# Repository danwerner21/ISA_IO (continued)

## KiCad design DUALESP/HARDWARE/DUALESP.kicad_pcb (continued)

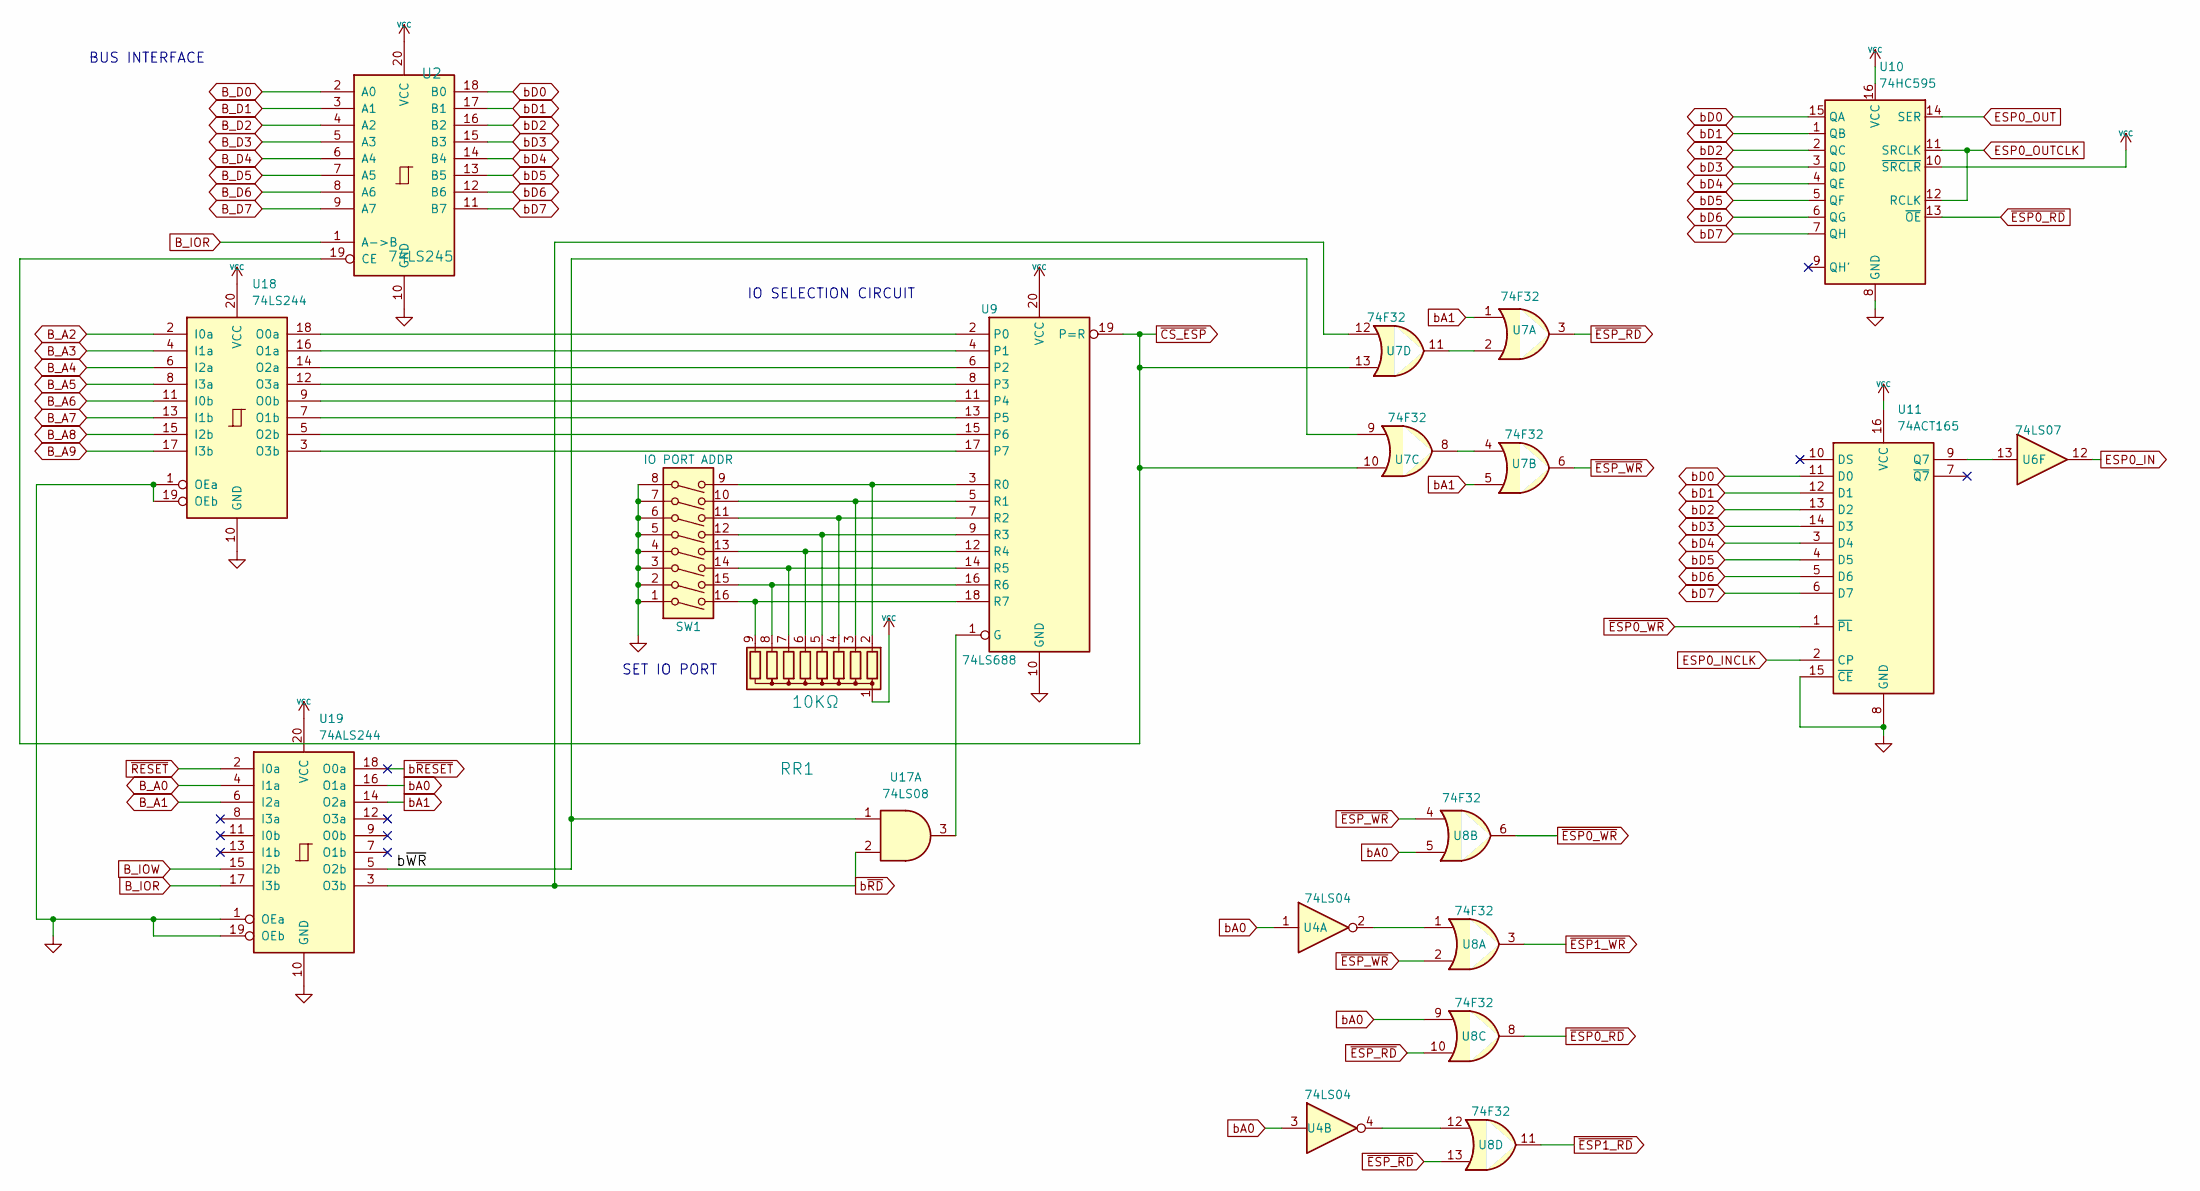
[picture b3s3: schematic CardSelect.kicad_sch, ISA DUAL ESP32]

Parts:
RR1: 10KΩ; R_Array_SIP9
SW1: IO PORT ADDR; STD_DDW_DIP16
U2: 74LS245; STD_DDW_DIP20
U4: 74LS04; STD_DDW_DIP14
U6: 74LS07; STD_DDW_DIP14
U7, U8: 74F32; STD_DDW_DIP14
U9: 74LS688; STD_DDW_DIP20
U10: 74HC595; STD_DDW_DIP16
U11: 74ACT165; STD_DDW_DIP16
U17: 74LS08; STD_DDW_DIP14
U18: 74LS244; STD_DDW_DIP20
U19: 74ALS244; STD_DDW_DIP20

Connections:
/CardSelect/b~WR: U7.9, U17.1, U19.5 (O2b)
B_A0: U19.4 (I1a); also elsewhere on the board
B_A1: U19.6 (I2a); also elsewhere on the board
B_A2: U18.2 (I0a); also elsewhere on the board
B_A3: U18.4 (I1a); also elsewhere on the board
B_A4: U18.6 (I2a); also elsewhere on the board
B_A5: U18.8 (I3a); also elsewhere on the board
B_A6: U18.11 (I0b); also elsewhere on the board
B_A7: U18.13 (I1b); also elsewhere on the board
B_A8: U18.15 (I2b); also elsewhere on the board
B_A9: U18.17 (I3b); also elsewhere on the board
B_D0: U2.2 (A0); also elsewhere on the board
B_D1: U2.3 (A1); also elsewhere on the board
B_D2: U2.4 (A2); also elsewhere on the board
B_D3: U2.5 (A3); also elsewhere on the board
B_D4: U2.6 (A4); also elsewhere on the board
B_D5: U2.7 (A5); also elsewhere on the board
B_D6: U2.8 (A6); also elsewhere on the board
B_D7: U2.9 (A7); also elsewhere on the board
B_IOR: U2.1 (A->B), U19.17 (I3b); also elsewhere on the board
B_IOW: U19.15 (I2b); also elsewhere on the board
ESP0_IN: U6.12; also elsewhere on the board
ESP0_INCLK: U11.2 (CP); also elsewhere on the board
ESP0_OUT: U10.14 (SER); also elsewhere on the board
ESP0_OUTCLK: U10.11 (SRCLK), U10.12 (RCLK); also elsewhere on the board
GND: SW1.1, SW1.2, SW1.3, SW1.4, SW1.5, SW1.6, SW1.7, SW1.8, U2.10 (GND), U9.10 (GND), U10.8 (GND), U11.8 (GND), U11.15 (~CE), U18.1 (OEa), U18.10 (GND), U18.19 (OEb), U19.1 (OEa), U19.10 (GND), U19.19 (OEb); also elsewhere on the board
unnamed: RR1.2 (R1), SW1.9, U9.3 (R0)
unnamed: RR1.3 (R2), SW1.10, U9.5 (R1)
unnamed: RR1.4 (R3), SW1.11, U9.7 (R2)
unnamed: RR1.5 (R4), SW1.12, U9.9 (R3)
unnamed: RR1.6 (R5), SW1.13, U9.12 (R4)
unnamed: RR1.7 (R6), SW1.14, U9.14 (R5)
unnamed: RR1.8 (R7), SW1.15, U9.16 (R6)
unnamed: RR1.9 (R8), SW1.16, U9.18 (R7)
unnamed: U4.2, U8.1
unnamed: U4.4, U8.12
unnamed: U7.4, U7.8
unnamed: U7.2, U7.11
unnamed: U9.1 (G), U17.3
unnamed: U6.13, U11.9 (Q7)
unnamed: U9.2 (P0), U18.18 (O0a)
unnamed: U9.11 (P4), U18.9 (O0b)
unnamed: U9.4 (P1), U18.16 (O1a)
unnamed: U9.13 (P5), U18.7 (O1b)
unnamed: U9.6 (P2), U18.14 (O2a)
unnamed: U9.15 (P6), U18.5 (O2b)
unnamed: U9.8 (P3), U18.12 (O3a)
unnamed: U9.17 (P7), U18.3 (O3b)
VCC: RR1.1 (common), U2.20 (VCC), U9.20 (VCC), U10.10 (~SRCLR), U10.16 (VCC), U11.16 (VCC), U18.20 (VCC), U19.20 (VCC); also elsewhere on the board
bA0: U4.1, U4.3, U8.5, U8.9, U19.16 (O1a)
bA1: U7.1, U7.5, U19.14 (O2a); also elsewhere on the board
bD0: U2.18 (B0), U10.15 (QA), U11.11 (D0); also elsewhere on the board
bD1: U2.17 (B1), U10.1 (QB), U11.12 (D1); also elsewhere on the board
bD2: U2.16 (B2), U10.2 (QC), U11.13 (D2); also elsewhere on the board
bD3: U2.15 (B3), U10.3 (QD), U11.14 (D3); also elsewhere on the board
bD4: U2.14 (B4), U10.4 (QE), U11.3 (D4); also elsewhere on the board
bD5: U2.13 (B5), U10.5 (QF), U11.4 (D5); also elsewhere on the board
bD6: U2.12 (B6), U10.6 (QG), U11.5 (D6); also elsewhere on the board
bD7: U2.11 (B7), U10.7 (QH), U11.6 (D7); also elsewhere on the board
b~RD: U7.12, U17.2, U19.3 (O3b); also elsewhere on the board
b~RESET: U19.18 (O0a)
~CS_ESP: U2.19 (CE), U7.10, U7.13, U9.19 (P=R); also elsewhere on the board
~ESP0_RD: U8.8, U10.13 (~OE); also elsewhere on the board
~ESP0_WR: U8.6, U11.1 (~PL); also elsewhere on the board
~ESP1_RD: U8.11; also elsewhere on the board
~ESP1_WR: U8.3; also elsewhere on the board
~ESP_RD: U7.3, U8.10, U8.13
~ESP_WR: U7.6, U8.2, U8.4
~RESET: U19.2 (I0a); also elsewhere on the board

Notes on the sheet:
SET IO PORT
IO SELECTION CIRCUIT
BUS INTERFACE

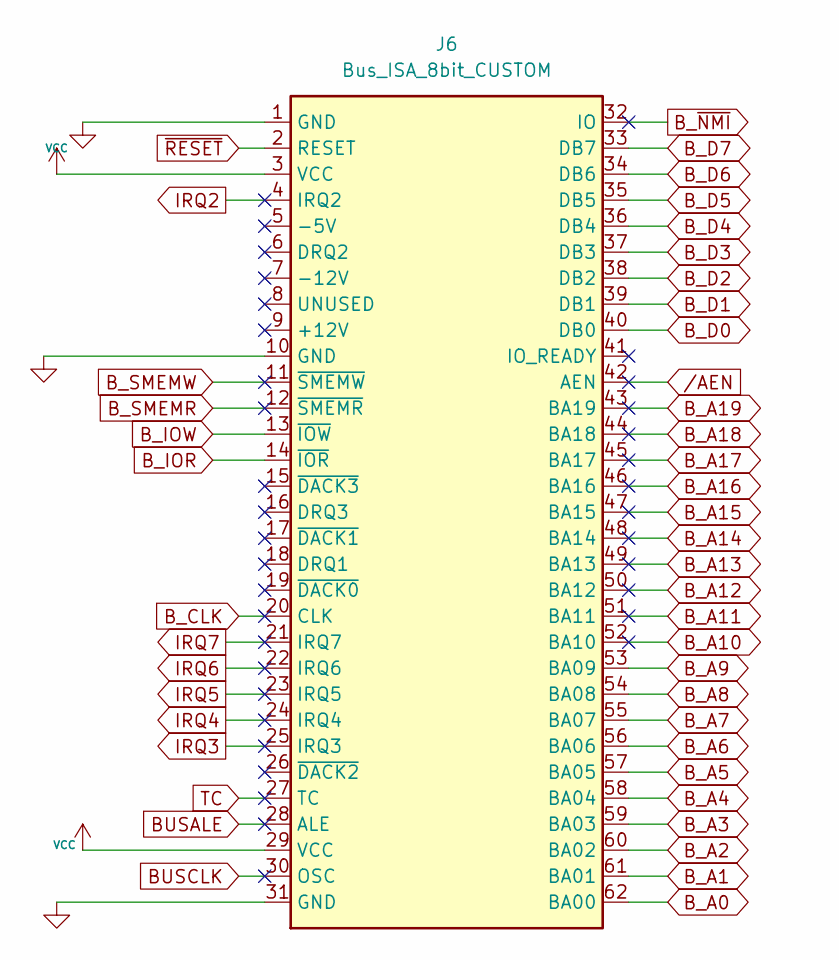
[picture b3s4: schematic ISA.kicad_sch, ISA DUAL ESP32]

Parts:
J6: Bus_ISA_8bit_CUSTOM; BUSEDGE_XT

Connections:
BUSALE: J6.28 (ALE)
BUSCLK: J6.30 (OSC)
B_A0: J6.62 (BA00); also elsewhere on the board
B_A1: J6.61 (BA01); also elsewhere on the board
B_A2: J6.60 (BA02); also elsewhere on the board
B_A3: J6.59 (BA03); also elsewhere on the board
B_A4: J6.58 (BA04); also elsewhere on the board
B_A5: J6.57 (BA05); also elsewhere on the board
B_A6: J6.56 (BA06); also elsewhere on the board
B_A7: J6.55 (BA07); also elsewhere on the board
B_A8: J6.54 (BA08); also elsewhere on the board
B_A9: J6.53 (BA09); also elsewhere on the board
B_A10: J6.52 (BA10)
B_A11: J6.51 (BA11)
B_A12: J6.50 (BA12)
B_A13: J6.49 (BA13)
B_A14: J6.48 (BA14)
B_A15: J6.47 (BA15)
B_A16: J6.46 (BA16)
B_A17: J6.45 (BA17)
B_A18: J6.44 (BA18)
B_A19: J6.43 (BA19)
B_CLK: J6.20 (CLK)
B_D0: J6.40 (DB0); also elsewhere on the board
B_D1: J6.39 (DB1); also elsewhere on the board
B_D2: J6.38 (DB2); also elsewhere on the board
B_D3: J6.37 (DB3); also elsewhere on the board
B_D4: J6.36 (DB4); also elsewhere on the board
B_D5: J6.35 (DB5); also elsewhere on the board
B_D6: J6.34 (DB6); also elsewhere on the board
B_D7: J6.33 (DB7); also elsewhere on the board
B_IOR: J6.14 (~IOR); also elsewhere on the board
B_IOW: J6.13 (~IOW); also elsewhere on the board
B_SMEMR: J6.12 (~SMEMR)
B_SMEMW: J6.11 (~SMEMW)
B_~NMI: J6.32 (IO)
GND: J6.1 (GND), J6.10 (GND), J6.31 (GND); also elsewhere on the board
IRQ2: J6.4 (IRQ2)
IRQ3: J6.25 (IRQ3)
IRQ4: J6.24 (IRQ4)
IRQ5: J6.23 (IRQ5)
IRQ6: J6.22 (IRQ6)
IRQ7: J6.21 (IRQ7)
TC: J6.27 (TC)
VCC: J6.3 (VCC), J6.29 (VCC); also elsewhere on the board
/AEN: J6.42 (AEN)
~RESET: J6.2 (RESET); also elsewhere on the board

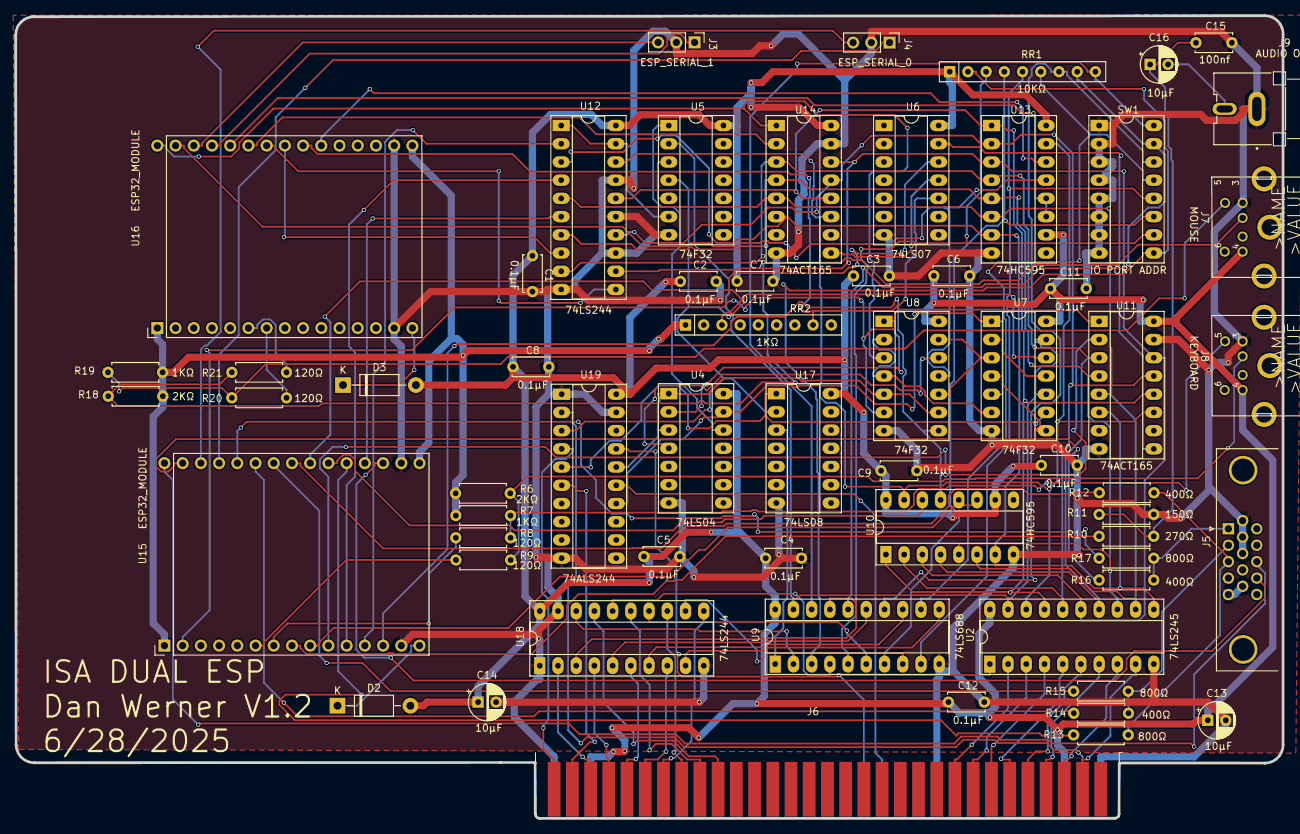
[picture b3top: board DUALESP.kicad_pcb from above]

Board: 2 copper layers, 176.7 x 111.9 mm, 61 parts (0 on the bottom side), 110 nets.

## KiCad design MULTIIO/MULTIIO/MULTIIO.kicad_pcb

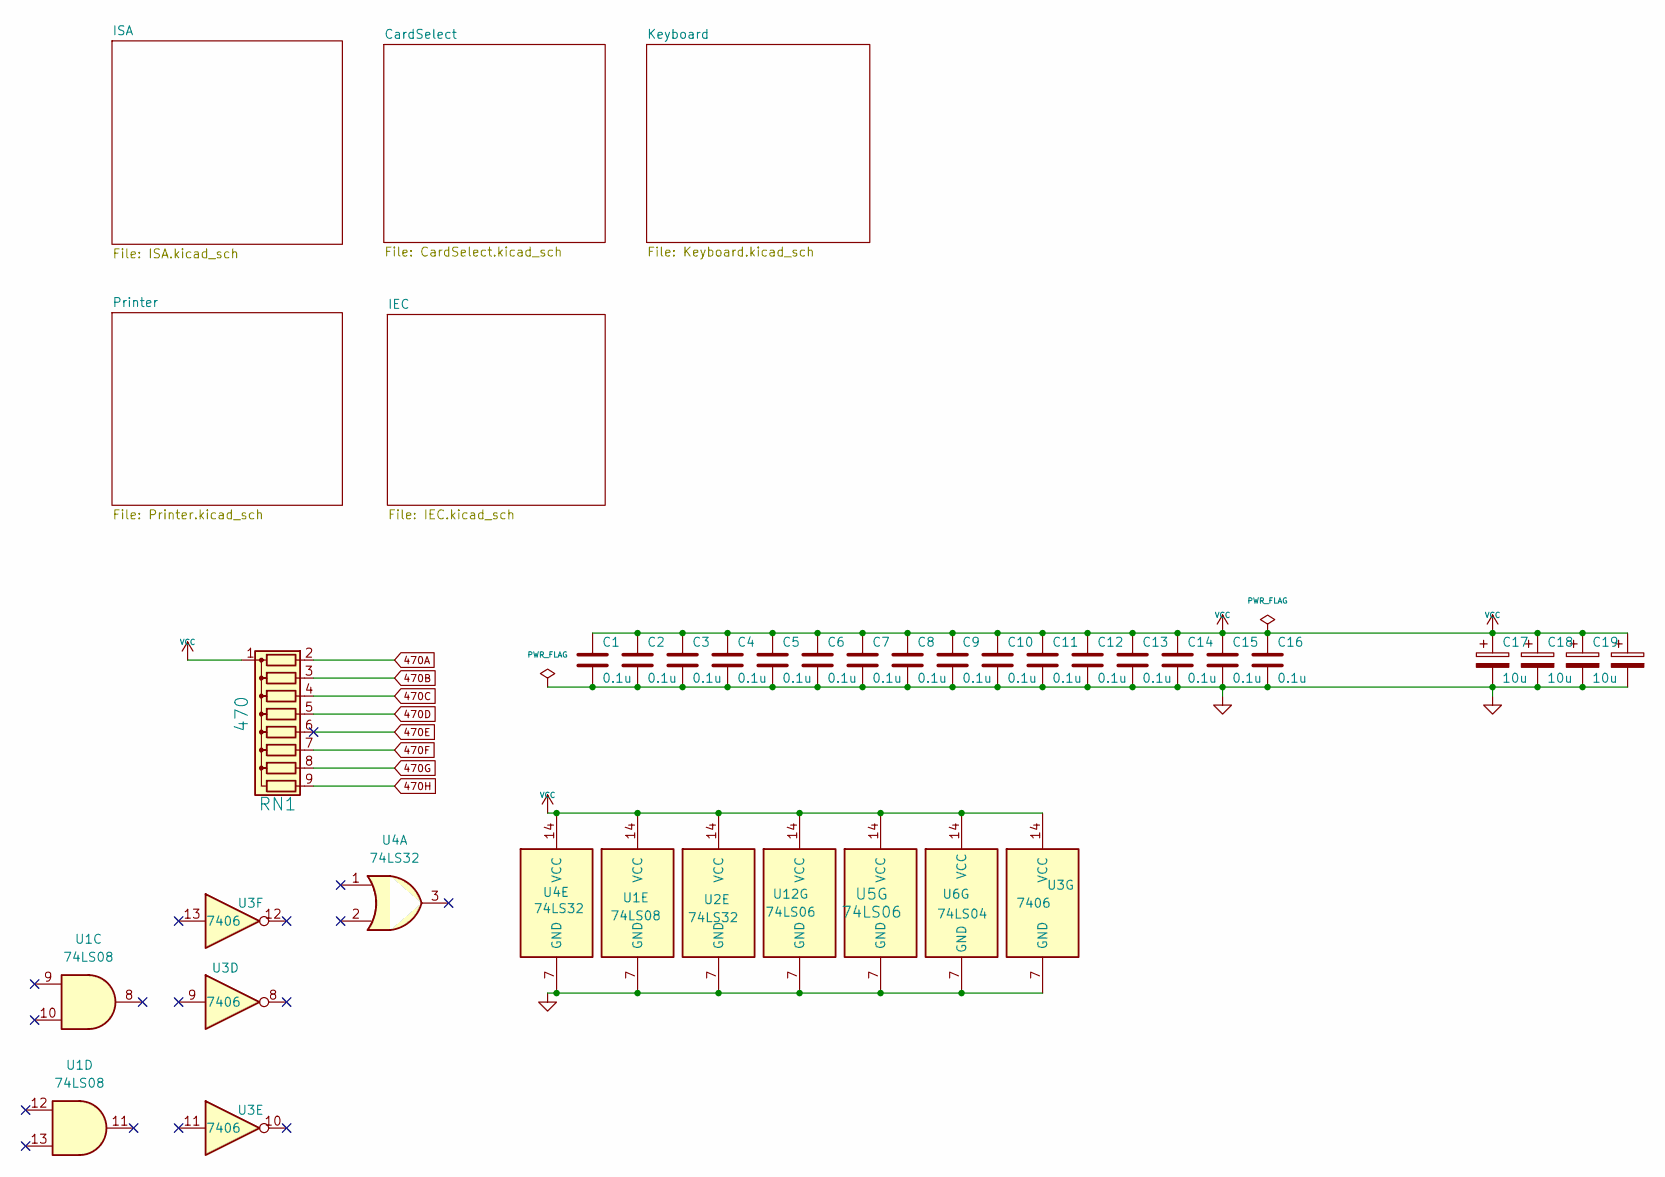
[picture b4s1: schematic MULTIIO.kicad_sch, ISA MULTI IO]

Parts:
C1, C2, C3, C4, C5, C6, C7, C8, C9, C10, C11, C12, C13, C14, C15, C16: 0.1u; STD_DDW_CAP
C17, C18, C19, C20: 10u; STD_DDW_PCAP
RN1: 470; STD_DDW_SIP9
U1: 74LS08; STD_DDW_DIP14
U2, U4: 74LS32; STD_DDW_DIP14
U3: 7406; STD_DDW_DIP14
U5, U12: 74LS06; STD_DDW_DIP14
U6: 74LS04; STD_DDW_DIP14

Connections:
470A: RN1.2 (R1); also elsewhere on the board
470B: RN1.3 (R2); also elsewhere on the board
470C: RN1.4 (R3); also elsewhere on the board
470D: RN1.5 (R4); also elsewhere on the board
470E: RN1.6 (R5)
470F: RN1.7 (R6); also elsewhere on the board
470G: RN1.8 (R7); also elsewhere on the board
470H: RN1.9 (R8); also elsewhere on the board
GND: C1.2, C2.2, C3.2, C4.2, C5.2, C6.2, C7.2, C8.2, C9.2, C10.2, C11.2, C12.2, C13.2, C14.2, C15.2, C16.2, C17.2, C18.2, C19.2, C20.2, U1.7 (GND), U2.7 (GND), U3.7 (GND), U4.7 (GND), U5.7 (GND), U6.7 (GND), U12.7 (GND); also elsewhere on the board
VCC: C1.1, C2.1, C3.1, C4.1, C5.1, C6.1, C7.1, C8.1, C9.1, C10.1, C11.1, C12.1, C13.1, C14.1, C15.1, C16.1, C17.1, C18.1, C19.1, C20.1, RN1.1 (common), U1.14 (VCC), U2.14 (VCC), U3.14 (VCC), U4.14 (VCC), U5.14 (VCC), U6.14 (VCC), U12.14 (VCC); also elsewhere on the board

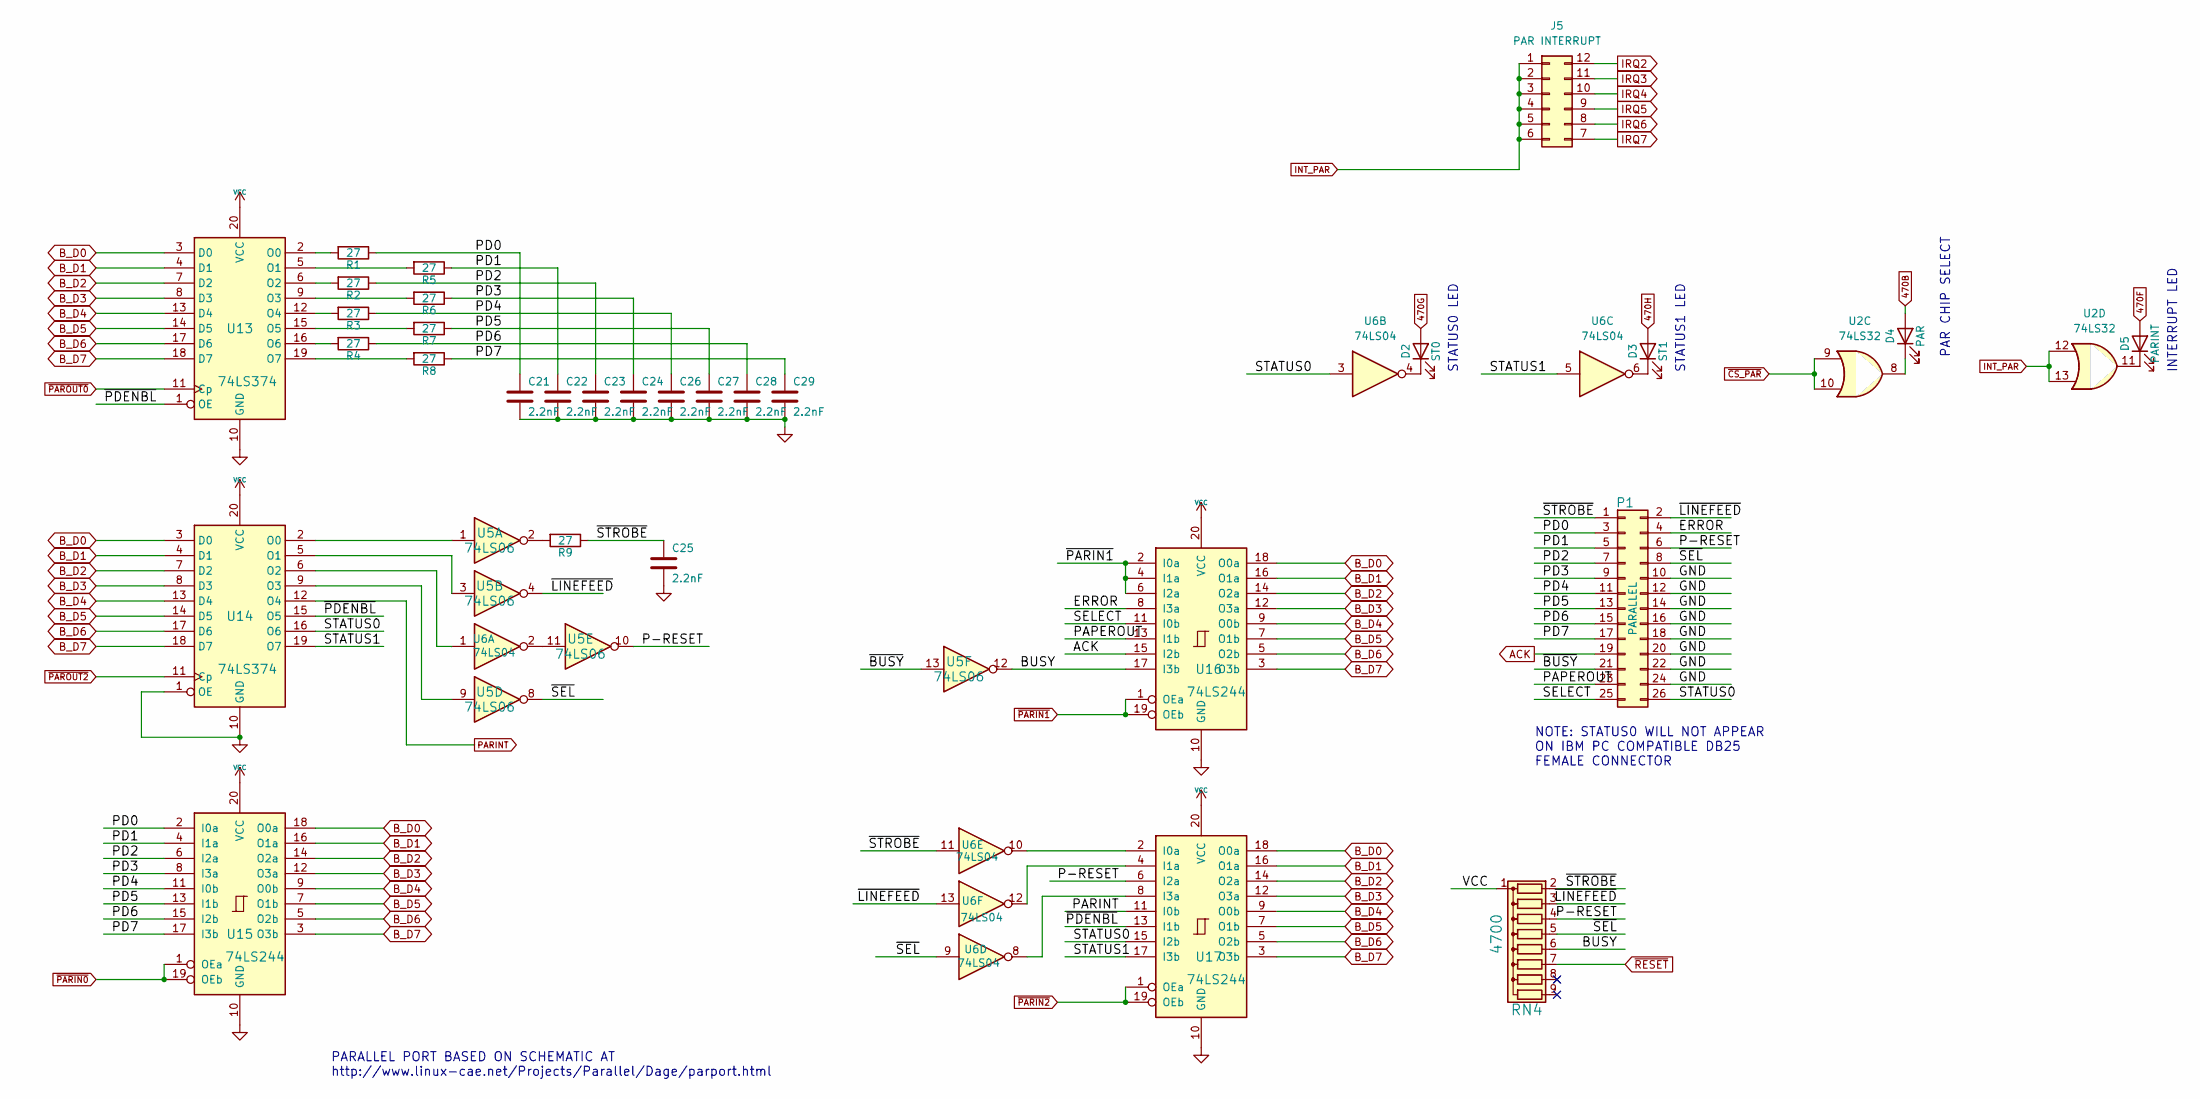
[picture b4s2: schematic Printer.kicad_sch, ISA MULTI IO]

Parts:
C21, C22, C23, C24, C25, C26, C27, C28, C29: 2.2nF; STD_DDW_CAP
D2: ST0; STD_DDW_LED5
D3: ST1; STD_DDW_LED5
D4: PAR; STD_DDW_LED5
D5: PARINT; STD_DDW_LED5
J5: PAR INTERRUPT; STD_DDW_PINHEAD_V_2x06
P1: PARALLEL; STD_DDW_PINHEAD_V_2x13
R1, R2, R3, R4, R5, R6, R7, R8, R9: 27; STD_DDW_RESISTOR
RN4: 4700; STD_DDW_SIP9
U2: 74LS32; STD_DDW_DIP14
U5: 74LS06; STD_DDW_DIP14
U6: 74LS04; STD_DDW_DIP14
U13, U14: 74LS374; STD_DDW_DIP20
U15, U16, U17: 74LS244; STD_DDW_DIP20

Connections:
470B: D4.2 (A); also elsewhere on the board
470F: D5.2 (A); also elsewhere on the board
470G: D2.2 (A); also elsewhere on the board
470H: D3.2 (A); also elsewhere on the board
/Printer/BUSY: RN4.6 (R5), U5.12, U16.17 (I3b)
/Printer/ERROR: P1.4, U16.8 (I3a)
/Printer/P-RESET: P1.6, RN4.4 (R3), U5.10, U17.6 (I2a)
/Printer/PAPEROUT: P1.23, U16.13 (I1b)
/Printer/PD0: C21.1, P1.3, R1.1, U15.2 (I0a)
/Printer/PD1: C22.1, P1.5, R5.1, U15.4 (I1a)
/Printer/PD2: C23.1, P1.7, R2.1, U15.6 (I2a)
/Printer/PD3: C24.1, P1.9, R6.1, U15.8 (I3a)
/Printer/PD4: C26.1, P1.11, R3.1, U15.11 (I0b)
/Printer/PD5: C27.1, P1.13, R7.1, U15.13 (I1b)
/Printer/PD6: C28.1, P1.15, R4.1, U15.15 (I2b)
/Printer/PD7: C29.1, P1.17, R8.1, U15.17 (I3b)
/Printer/SELECT: P1.25, U16.11 (I0b)
/Printer/STATUS0: P1.26, U6.3, U14.16 (O6), U17.15 (I2b)
/Printer/STATUS1: U6.5, U14.19 (O7), U17.17 (I3b)
/Printer/~BUSY: P1.21, U5.13
/Printer/~LINEFEED: P1.2, RN4.3 (R2), U5.4, U6.13
/Printer/~PDENBL: U13.1 (OE), U14.15 (O5), U17.13 (I1b)
/Printer/~SEL: P1.8, RN4.5 (R4), U5.8, U6.9
/Printer/~STROBE: C25.1, P1.1, R9.1, RN4.2 (R1), U6.11
ACK: P1.19, U16.15 (I2b)
B_D0: U13.3 (D0), U14.3 (D0), U15.18 (O0a), U16.18 (O0a), U17.18 (O0a); also elsewhere on the board
B_D1: U13.4 (D1), U14.4 (D1), U15.16 (O1a), U16.16 (O1a), U17.16 (O1a); also elsewhere on the board
B_D2: U13.7 (D2), U14.7 (D2), U15.14 (O2a), U16.14 (O2a), U17.14 (O2a); also elsewhere on the board
B_D3: U13.8 (D3), U14.8 (D3), U15.12 (O3a), U16.12 (O3a), U17.12 (O3a); also elsewhere on the board
B_D4: U13.13 (D4), U14.13 (D4), U15.9 (O0b), U16.9 (O0b), U17.9 (O0b); also elsewhere on the board
B_D5: U13.14 (D5), U14.14 (D5), U15.7 (O1b), U16.7 (O1b), U17.7 (O1b); also elsewhere on the board
B_D6: U13.17 (D6), U14.17 (D6), U15.5 (O2b), U16.5 (O2b), U17.5 (O2b); also elsewhere on the board
B_D7: U13.18 (D7), U14.18 (D7), U15.3 (O3b), U16.3 (O3b), U17.3 (O3b); also elsewhere on the board
GND: C21.2, C22.2, C23.2, C24.2, C25.2, C26.2, C27.2, C28.2, C29.2, P1.10, P1.12, P1.14, P1.16, P1.18, P1.20, P1.22, P1.24, U13.10 (GND), U14.1 (OE), U14.10 (GND), U15.10 (GND), U16.10 (GND), U17.10 (GND); also elsewhere on the board
INT_PAR: J5.1, J5.2, J5.3, J5.4, J5.5, J5.6, U2.12, U2.13
IRQ2: J5.12; also elsewhere on the board
IRQ3: J5.11; also elsewhere on the board
IRQ4: J5.10; also elsewhere on the board
IRQ5: J5.9; also elsewhere on the board
IRQ6: J5.8; also elsewhere on the board
IRQ7: J5.7; also elsewhere on the board
unnamed: D2.1 (K), U6.4
unnamed: D3.1 (K), U6.6
unnamed: D4.1 (K), U2.8
unnamed: D5.1 (K), U2.11
unnamed: R9.2, U5.2
unnamed: U5.11, U6.2
unnamed: R1.2, U13.2 (O0)
unnamed: R5.2, U13.5 (O1)
unnamed: R2.2, U13.6 (O2)
unnamed: R6.2, U13.9 (O3)
unnamed: R3.2, U13.12 (O4)
unnamed: R7.2, U13.15 (O5)
unnamed: R4.2, U13.16 (O6)
unnamed: R8.2, U13.19 (O7)
unnamed: U5.1, U14.2 (O0)
unnamed: U5.3, U14.5 (O1)
unnamed: U6.1, U14.6 (O2)
unnamed: U5.9, U14.9 (O3)
unnamed: U6.10, U17.2 (I0a)
unnamed: U6.12, U17.4 (I1a)
unnamed: U6.8, U17.8 (I3a)
PARINT: U14.12 (O4), U17.11 (I0b)
VCC: RN4.1 (common), U13.20 (VCC), U14.20 (VCC), U15.20 (VCC), U16.20 (VCC), U17.20 (VCC); also elsewhere on the board
~CS_PAR: U2.9, U2.10; also elsewhere on the board
~PARIN0: U15.1 (OEa), U15.19 (OEb); also elsewhere on the board
~PARIN1: U16.1 (OEa), U16.2 (I0a), U16.4 (I1a), U16.6 (I2a), U16.19 (OEb); also elsewhere on the board
~PARIN2: U17.1 (OEa), U17.19 (OEb); also elsewhere on the board
~PAROUT0: U13.11 (Cp); also elsewhere on the board
~PAROUT2: U14.11 (Cp); also elsewhere on the board
~RESET: RN4.7 (R6); also elsewhere on the board

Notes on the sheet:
NOTE: STATUS0 WILL NOT APPEAR ON IBM PC COMPATIBLE DB25 FEMALE CONNECTOR
STATUS0 LED
INTERRUPT LED
STATUS1 LED
PARALLEL PORT BASED ON SCHEMATIC AT http://www.linux-cae.net/Projects/Parallel/Dage/parport.html
PAR CHIP SELECT

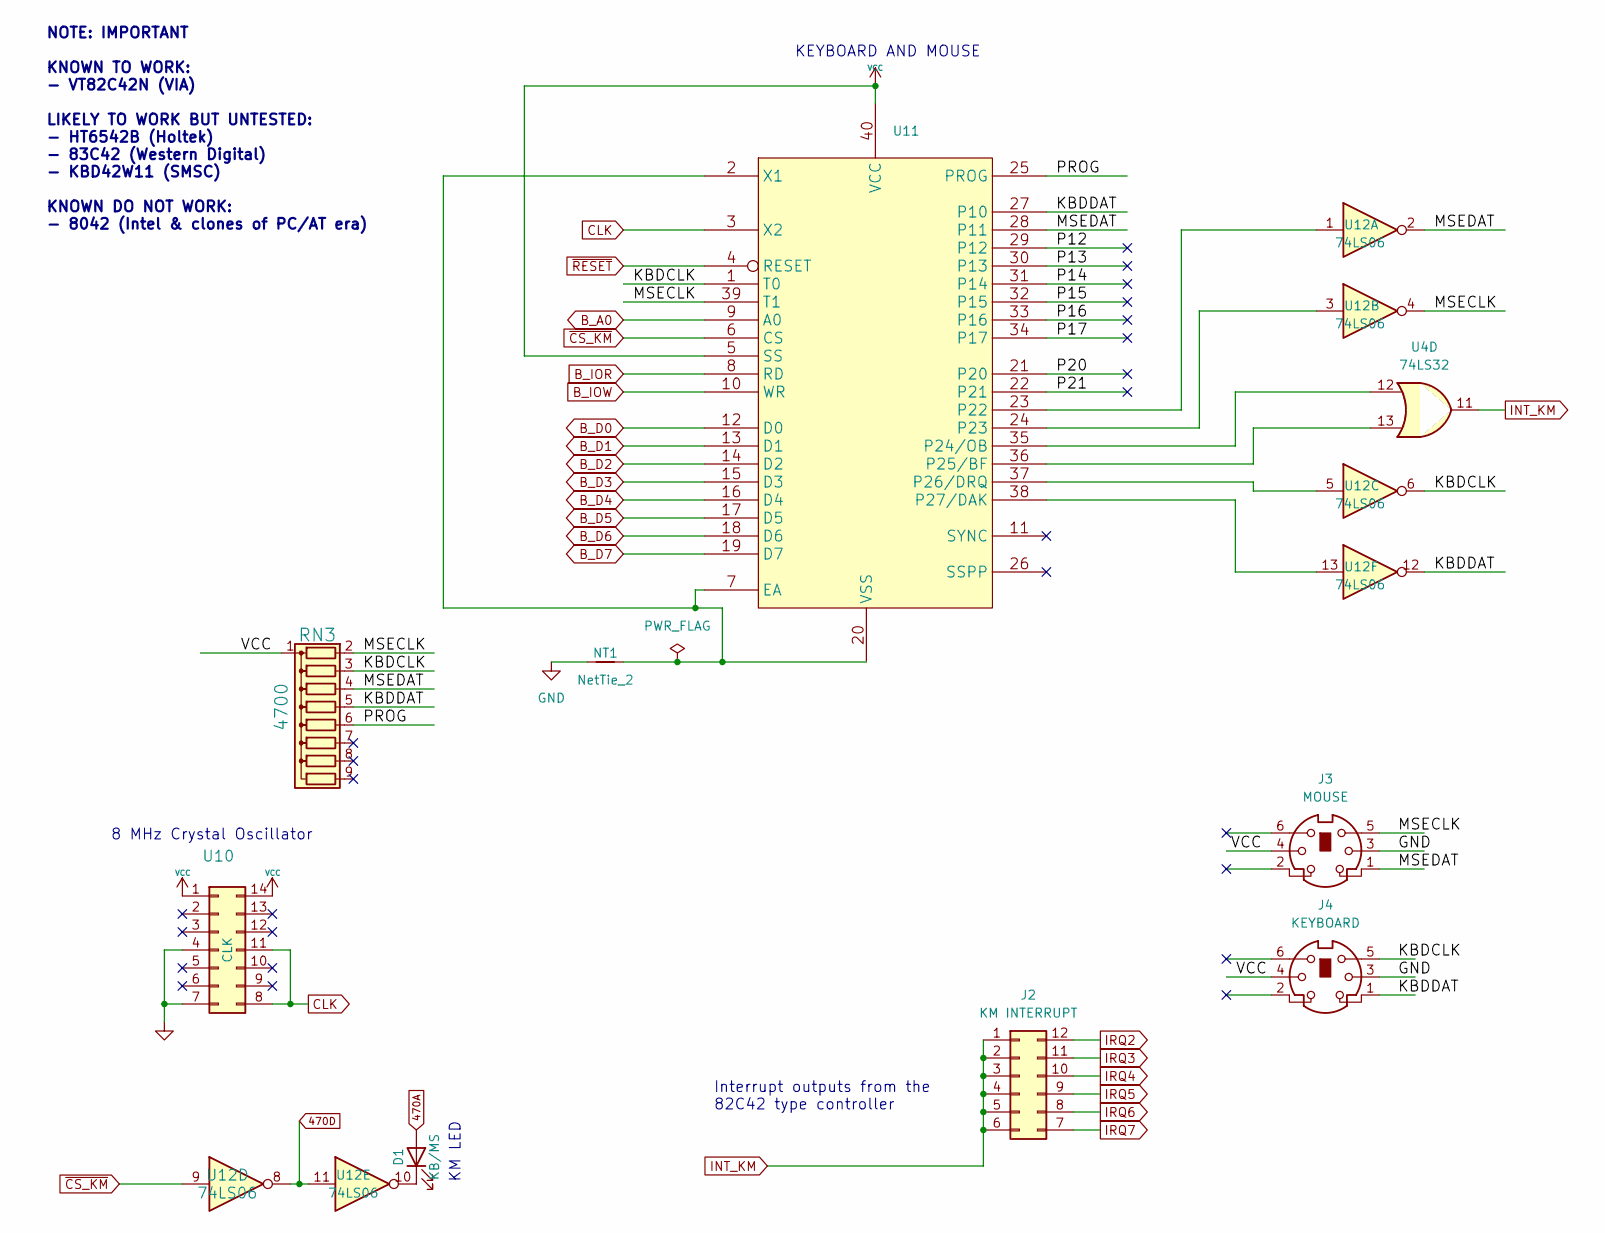
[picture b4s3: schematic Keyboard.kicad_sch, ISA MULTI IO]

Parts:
D1: KB/MS; STD_DDW_LED5
J2: KM INTERRUPT; STD_DDW_PINHEAD_V_2x06
J3: MOUSE; PS2_DIN
J4: KEYBOARD; PS2_DIN
NT1: NetTie_2; NetTie-2_THT_Pad0.3mm
RN3: 4700; STD_DDW_SIP9
U4: 74LS32; STD_DDW_DIP14
U10: CLK; STD_DDW_DIP14
U11: STD_DDW_DIP40
U12: 74LS06; STD_DDW_DIP14

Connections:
470A: D1.2 (A); also elsewhere on the board
470D: U12.8, U12.11; also elsewhere on the board
/Keyboard/KBDCLK: J4.5, RN3.3 (R2), U11.1 (T0), U12.6
/Keyboard/KBDDAT: J4.1, RN3.5 (R4), U11.27 (P10), U12.12
/Keyboard/MSECLK: J3.5, RN3.2 (R1), U11.39 (T1), U12.4
/Keyboard/MSEDAT: J3.1, RN3.4 (R3), U11.28 (P11), U12.2
/Keyboard/P12: U11.29 (P12)
/Keyboard/P13: U11.30 (P13)
/Keyboard/P14: U11.31 (P14)
/Keyboard/P15: U11.32 (P15)
/Keyboard/P16: U11.33 (P16)
/Keyboard/P17: U11.34 (P17)
/Keyboard/P20: U11.21 (P20)
/Keyboard/P21: U11.22 (P21)
/Keyboard/PROG: RN3.6 (R5), U11.25 (PROG)
B_A0: U11.9 (A0); also elsewhere on the board
B_D0: U11.12 (D0); also elsewhere on the board
B_D1: U11.13 (D1); also elsewhere on the board
B_D2: U11.14 (D2); also elsewhere on the board
B_D3: U11.15 (D3); also elsewhere on the board
B_D4: U11.16 (D4); also elsewhere on the board
B_D5: U11.17 (D5); also elsewhere on the board
B_D6: U11.18 (D6); also elsewhere on the board
B_D7: U11.19 (D7); also elsewhere on the board
B_IOR: U11.8 (RD); also elsewhere on the board
B_IOW: U11.10 (WR); also elsewhere on the board
CLK: U10.8, U10.11, U11.3 (X2)
GND: J3.3, J4.3, NT1.1, U10.4, U10.7; also elsewhere on the board
INT_KM: J2.1, J2.2, J2.3, J2.4, J2.5, J2.6, U4.11
IRQ2: J2.12; also elsewhere on the board
IRQ3: J2.11; also elsewhere on the board
IRQ4: J2.10; also elsewhere on the board
IRQ5: J2.9; also elsewhere on the board
IRQ6: J2.8; also elsewhere on the board
IRQ7: J2.7; also elsewhere on the board
unnamed: D1.1 (K), U12.10
unnamed: NT1.2, U11.2 (X1), U11.7 (EA), U11.20 (VSS)
unnamed: U11.23 (P22), U12.1
unnamed: U11.24 (P23), U12.3
unnamed: U4.12, U11.35 (P24/OB)
unnamed: U4.13, U11.36 (P25/BF)
unnamed: U11.37 (P26/DRQ), U12.5
unnamed: U11.38 (P27/DAK), U12.13
VCC: J3.4, J4.4, RN3.1 (common), U10.1, U10.14, U11.5 (SS), U11.40 (VCC); also elsewhere on the board
~CS_KM: U11.6 (CS), U12.9; also elsewhere on the board
~RESET: U11.4 (RESET); also elsewhere on the board

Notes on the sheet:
KM LED
NOTE: IMPORTANT KNOWN TO WORK: - VT82C42N (VIA) LIKELY TO WORK BUT UNTESTED: - HT6542B (Holtek) - 83C42 (Western Digital) - KBD42W11 (SMSC) KNOWN DO NOT WORK: - 8042 (Intel & clones of PC/AT era)
KEYBOARD AND MOUSE
Interrupt outputs from the 82C42 type controller
8 MHz Crystal Oscillator

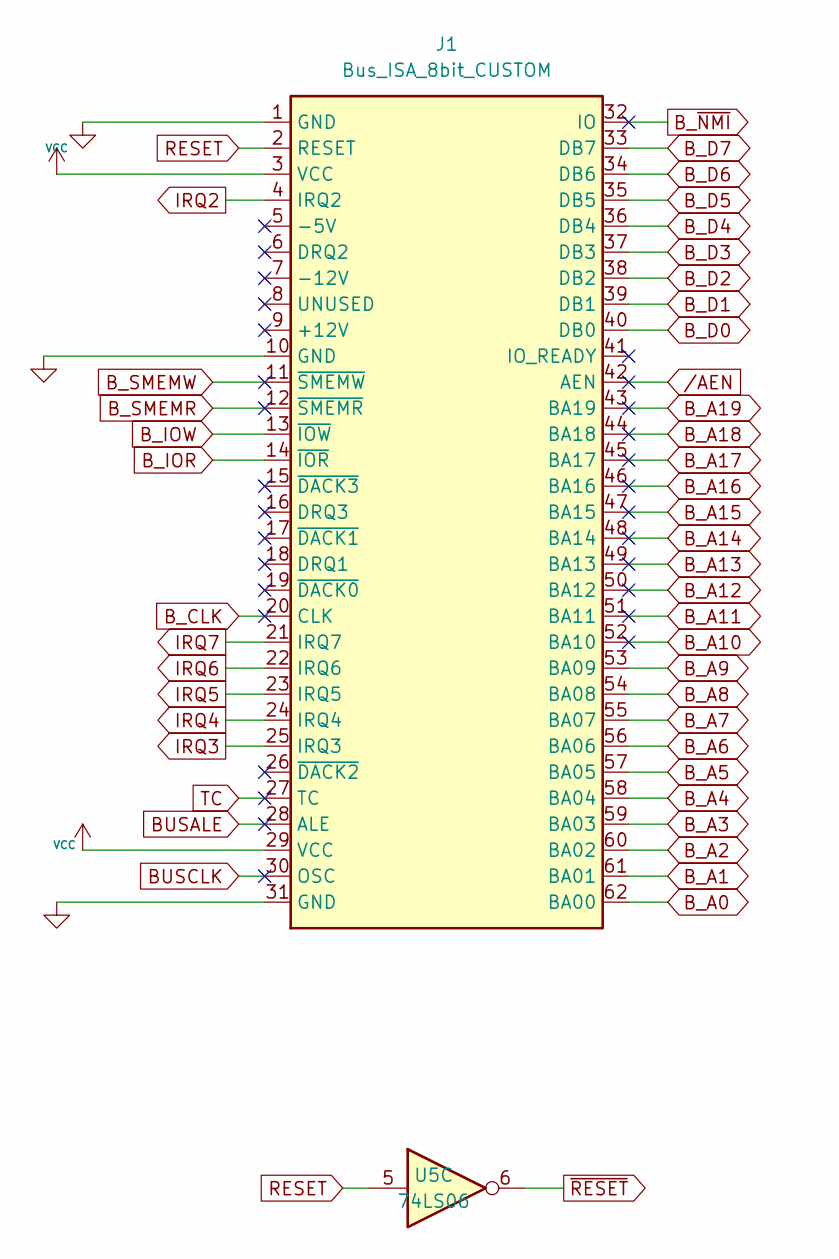
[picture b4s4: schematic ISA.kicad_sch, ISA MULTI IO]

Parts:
J1: Bus_ISA_8bit_CUSTOM; BUSEDGE_XT
U5: 74LS06; STD_DDW_DIP14

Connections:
BUSALE: J1.28 (ALE)
BUSCLK: J1.30 (OSC)
B_A0: J1.62 (BA00); also elsewhere on the board
B_A1: J1.61 (BA01); also elsewhere on the board
B_A2: J1.60 (BA02); also elsewhere on the board
B_A3: J1.59 (BA03); also elsewhere on the board
B_A4: J1.58 (BA04); also elsewhere on the board
B_A5: J1.57 (BA05); also elsewhere on the board
B_A6: J1.56 (BA06); also elsewhere on the board
B_A7: J1.55 (BA07); also elsewhere on the board
B_A8: J1.54 (BA08); also elsewhere on the board
B_A9: J1.53 (BA09); also elsewhere on the board
B_A10: J1.52 (BA10)
B_A11: J1.51 (BA11)
B_A12: J1.50 (BA12)
B_A13: J1.49 (BA13)
B_A14: J1.48 (BA14)
B_A15: J1.47 (BA15)
B_A16: J1.46 (BA16)
B_A17: J1.45 (BA17)
B_A18: J1.44 (BA18)
B_A19: J1.43 (BA19)
B_CLK: J1.20 (CLK)
B_D0: J1.40 (DB0); also elsewhere on the board
B_D1: J1.39 (DB1); also elsewhere on the board
B_D2: J1.38 (DB2); also elsewhere on the board
B_D3: J1.37 (DB3); also elsewhere on the board
B_D4: J1.36 (DB4); also elsewhere on the board
B_D5: J1.35 (DB5); also elsewhere on the board
B_D6: J1.34 (DB6); also elsewhere on the board
B_D7: J1.33 (DB7); also elsewhere on the board
B_IOR: J1.14 (~IOR); also elsewhere on the board
B_IOW: J1.13 (~IOW); also elsewhere on the board
B_SMEMR: J1.12 (~SMEMR)
B_SMEMW: J1.11 (~SMEMW)
B_~NMI: J1.32 (IO)
GND: J1.1 (GND), J1.10 (GND), J1.31 (GND); also elsewhere on the board
IRQ2: J1.4 (IRQ2); also elsewhere on the board
IRQ3: J1.25 (IRQ3); also elsewhere on the board
IRQ4: J1.24 (IRQ4); also elsewhere on the board
IRQ5: J1.23 (IRQ5); also elsewhere on the board
IRQ6: J1.22 (IRQ6); also elsewhere on the board
IRQ7: J1.21 (IRQ7); also elsewhere on the board
RESET: J1.2 (RESET), U5.5
TC: J1.27 (TC)
VCC: J1.3 (VCC), J1.29 (VCC); also elsewhere on the board
/AEN: J1.42 (AEN)
~RESET: U5.6; also elsewhere on the board
